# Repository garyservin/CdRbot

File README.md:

CdRbot
======

Robot para el curso de Robótica del Club de Robótica de la Facultad Politécnica de la Universidad Nacional de Asunción

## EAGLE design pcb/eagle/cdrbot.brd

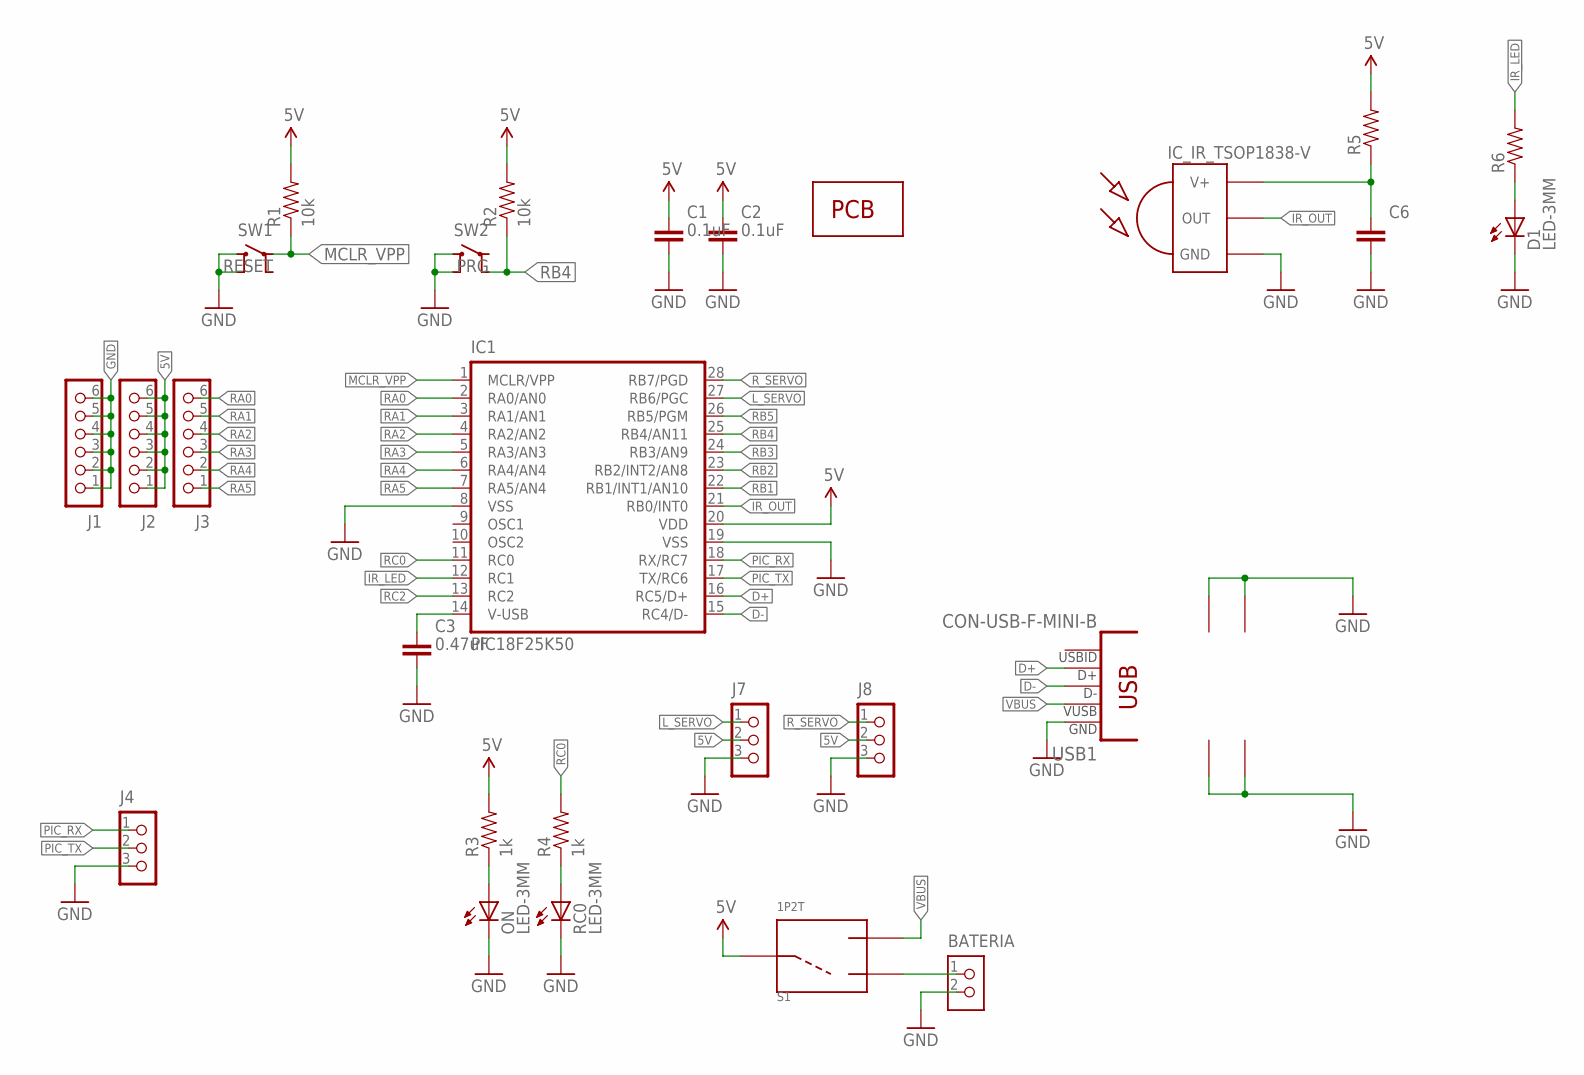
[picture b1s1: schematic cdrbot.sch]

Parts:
BATERIA: CON_HEADER_1X02-PTH-M; M1X02_M
C1, C2: 0.1uF; C025-025X050
C3: 0.47uF; C025-025X050
C6: CAPACITOR-DECOUPLING; C025-025X050
D1: LED-3MM
IC1: PIC18F25K50; DIL-28
IC2: IC_IR_TSOP1838-V; TSOP18XX_V
J1, J2, J3: CON_HEADER_1X06-PTH_M; M1X06_M
J4, J7, J8: CON_HEADER_1X03-PTH_M; M1X03_M
ON: LED-3MM
PCB1: PCB_DP_SQUARE-5X5; PCB5X5
R1, R2: 10k; RTH025W_03
R3, R4: 1k; RTH025W_03
R5, R6: RESISTOR-1/4W-0.3"; RTH025W_03
RC0: LED-3MM
S1: 1P2T
SW1: RESET; TACTILE-PTH
SW2: PRG; TACTILE-PTH
USB1: CON-USB-F-MINI-B; CONN_USB_MINI-B

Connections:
5V: C1.1, C2.1, IC1.20 (VDD), J2.1, J2.2, J2.3, J2.4, J2.5, J2.6, J7.2, J8.2, R1.2, R2.2, R3.2, R5.2, S1.P$1
D+: IC1.16 (RC5/D+), USB1.D+
D-: IC1.15 (RC4/D-), USB1.D-
GND: BATERIA.2, C1.2, C2.2, C3.2, C6.2, D1.K (C), IC1.8 (VSS), IC1.19 (VSS), IC2.GND, J1.1, J1.2, J1.3, J1.4, J1.5, J1.6, J4.3, J7.3, J8.3, ON.K (C), RC0.K (C), SW1.3 (2), SW1.4, SW2.3 (2), SW2.4, USB1.BODY@1 (BODY), USB1.BODY@2 (BODY), USB1.BODY@3 (BODY), USB1.BODY@4 (BODY), USB1.GND
IRLED: D1.A, R6.1
IR_LED: IC1.12 (RC1), R6.2
IR_OUT: IC1.21 (RB0/INT0), IC2.OUT
LED1: ON.A, R3.1
LED2: R4.1, RC0.A
L_SERVO: IC1.27 (RB6/PGC), J7.1
MCLR_VPP: IC1.1 (MCLR/VPP), R1.1, SW1.1
unnamed: BATERIA.1, S1.P$2
PIC_RX: IC1.18 (RX/RC7), J4.1
PIC_TX: IC1.17 (TX/RC6), J4.2
RA0: IC1.2 (RA0/AN0), J3.6
RA1: IC1.3 (RA1/AN1), J3.5
RA2: IC1.4 (RA2/AN2), J3.4
RA3: IC1.5 (RA3/AN3), J3.3
RA4: IC1.6 (RA4/AN4), J3.2
RA5: IC1.7 (RA5/AN4), J3.1
RB1: IC1.22 (RB1/INT1/AN10)
RB2: IC1.23 (RB2/INT2/AN8)
RB3: IC1.24 (RB3/AN9)
RB4: IC1.25 (RB4/AN11), R2.1, SW2.2 (3)
RB5: IC1.26 (RB5/PGM)
RC0: IC1.11 (RC0), R4.2
RC2: IC1.13 (RC2)
R_SERVO: IC1.28 (RB7/PGD), J8.1
VBUS: S1.P$3, USB1.VUSB
VCC_TSOP: C6.1, IC2.VCC (V+), R5.1
VUSB: C3.1, IC1.14 (V-USB)

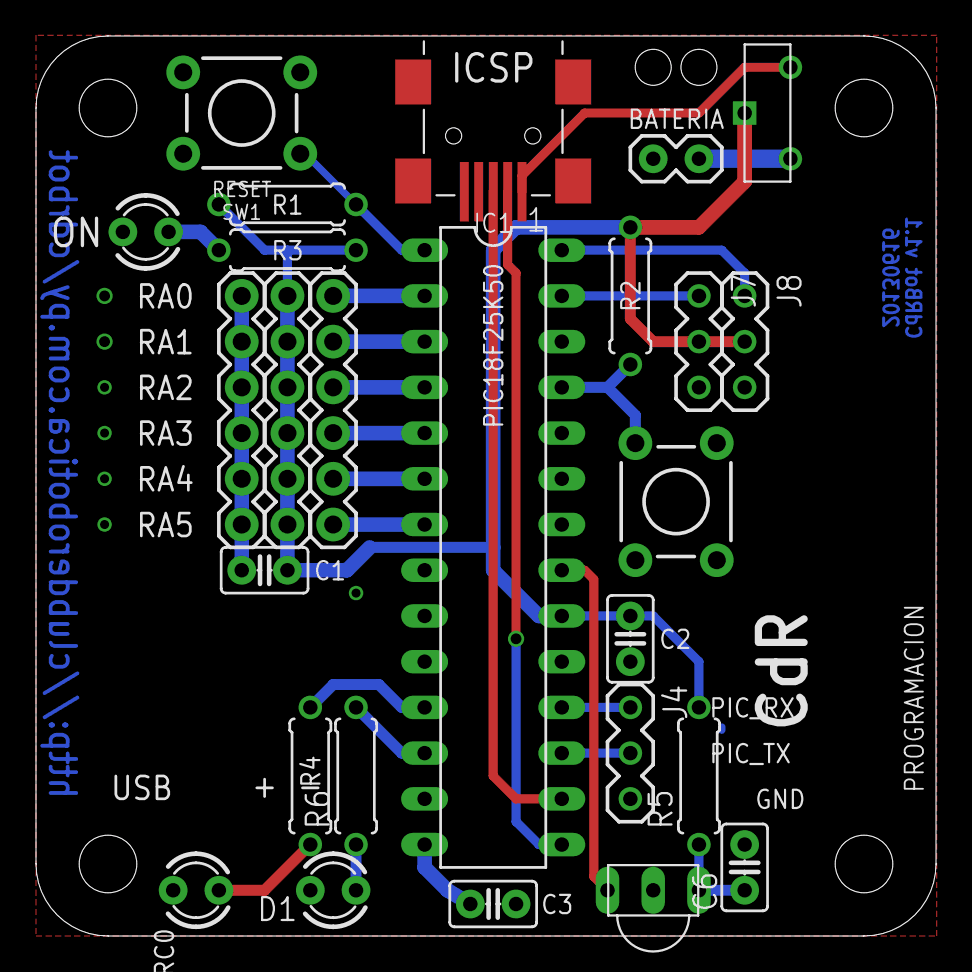
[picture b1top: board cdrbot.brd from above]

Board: 2 copper layers, 50.0 x 50.0 mm, 27 parts (0 on the bottom side), 26 nets.

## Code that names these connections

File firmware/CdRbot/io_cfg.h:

/* 
 * File:   io_cfg.h
 * Author: gary
 *
 * Created on June 16, 2013, 12:29 AM
 */

#ifndef IO_CFG_H
#define	IO_CFG_H

/** I N C L U D E S **********************************************************/
#include <xc.h>

/** T R I S ******************************************************************/
#define INPUT_PIN           1
#define OUTPUT_PIN          0

/** L E D ********************************************************************/
#define mInitLED()		LATC &= 0xFE; TRISC &= 0xFE;

#define mLED_1			LATCbits.LATC0
#define mLED_1_On()		mLED_1 = 1;
#define mLED_1_Off()		mLED_1 = 0;
#define mLED_1_Toggle()		mLED_1 ^= 1;

/** S W I T C H **************************************************************/
#define mInitSwitchPrg()	TRISBbits.TRISB4 = 1; ANSELBbits.ANSB4 = 0;

#define swPrg			PORTBbits.RB4

/** S E R V O S **************************************************************/
#define mInitServos()		LATB &= 0x3F; TRISB &= 0x3F;

#define mServo_L		LATBbits.LATB6		// Left Servo
#define mServo_R		LATBbits.LATB7		// Right Servo

/** L I N E  S E N S O R S ***************************************************/
#define mInitLineSensors()	TRISAbits.TRISA0=TRISAbits.TRISA1=1;ADCON0=0x01;ADCON2=0x3C;

#define mLineSensor_L		PORTAbits.RA0		// Left Sensor
#define mLineSensor_R		PORTAbits.RA1		// Right Sensor

/** O P O N E N T  S E N S O R ***********************************************/
#define mInitOponentSensor()	TRISBbits.TRISB0 = 1; ANSELBbits.ANSB0 = 0; TRISBbits.RB3 = 0; ANSELBbits.ANSB3 = 0;
#define mOponentSenor		PORTBbits.RB0

#endif	/* IO_CFG_H */

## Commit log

2013-04-30 Add README.md file with description of the project
2013-04-30 Agregadas carpetas para pcb de eagle y kicad
2013-04-30 Agregados archivos de Eagle para la placa
2013-04-30 Eliminado archivo de prueba
2013-05-03 First commit for Kicad PCB for the CdRbot
2013-05-03 Add svg file for the base of the robot
2013-05-03 Added bootloader and CdRbot code (Initial Commit)
2013-05-03 Modifications to the schematic
2013-05-04 Agregando archivos Kicad
2013-05-04 Agregado archivo de prueba
2013-05-08 Modificaciones varias a la placa, compatibilidad con pic 18f2550 y 18f25k20
2013-05-08 Nueva version del PCB
2013-05-10 Generados los gerbers para fabricación en IteadStudio
2013-05-10 Generados gerbers para fabricación
2013-06-16 Agregado bootloader funcional (Solo con C18)
2013-06-16 Added working bootloader (Compile only with C18), moved XC8 bootloader
2013-06-16 Add working bootloader (compile with C18)
2013-06-17 Added code for the servomotors
2013-06-17 Added On/Off switch, increase cable holes, removed diode
2013-09-13 Added support for tsop sensor and for 38kHz PWM generation
2013-09-23 Added support fot TSOP38238
2013-09-23 Added .gitignore file
2013-09-23 Cleaned various unused files
2013-09-23 Cleaned makefiles
2014-04-06 Replaced way to toggle led
2014-04-06 Init motors
2014-04-06 Fixed receiving function for TSOP sensor and for sendIR
2014-04-06 Update project files
2014-04-06 Removed Microchip propietary MLA code for te bootloader
